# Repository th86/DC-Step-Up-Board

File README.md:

DC-DC Step-Up Board
=========

This is an NE555-based adjustable DC-DC step-up board, which converts 9~12Vdc to up to 400Vdc. 

WARNING: THE HIGH VOLTAGE IS LETHAL, USE IT WITH CAUTION!

## License ##
This project is licensed under the MIT license.

Copyright (c) 2015 Tai-Hsien Ouyang

THE DOCUMENT IS PROVIDED "AS IS", WITHOUT WARRANTY OF ANY KIND, EXPRESS OR IMPLIED, INCLUDING BUT NOT LIMITED TO THE WARRANTIES OF MERCHANTABILITY, FITNESS FOR A PARTICULAR PURPOSE AND NONINFRINGEMENT. IN NO EVENT SHALL THE AUTHORS OR COPYRIGHT HOLDERS BE LIABLE FOR ANY CLAIM, DAMAGES OR OTHER LIABILITY, WHETHER IN AN ACTION OF CONTRACT, TORT OR OTHERWISE, ARISING FROM, OUT OF OR IN CONNECTION WITH THE DOCUMENT OR THE USE OR OTHER DEALINGS IN THE DOCUMENT.

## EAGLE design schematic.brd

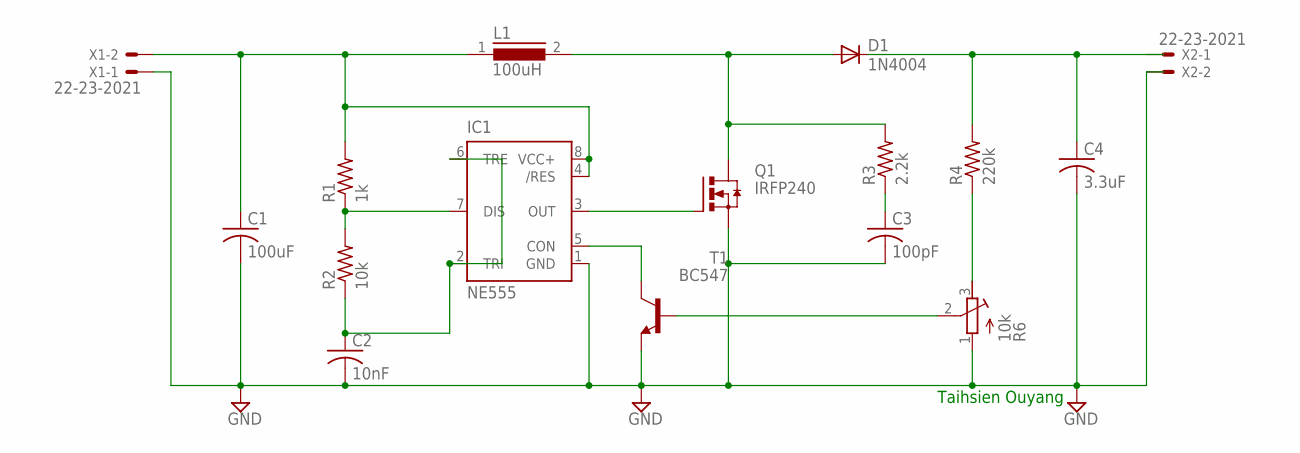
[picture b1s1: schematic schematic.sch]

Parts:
C1: 100uF; C050-025X075
C2: 10nF; C050-025X075
C3: 100pF; C050-025X075
C4: 3.3uF; C050-025X075
D1: 1N4004; DO41-10
IC1: NE555; DIL-08
L1: 100uH; SFT1040
Q1: IRFP240; TO247BV
R1: 1k; 0207/7
R2: 10k; 0207/7
R3: 2.2k; 0207/7
R4: 220k; 0207/7
R6: 10k; RTRIM3339P
T1: BC547; TO92
X1, X2: 22-23-2021

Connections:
GND: C1.2, C2.2, C3.2, C4.2, IC1.1 (GND), Q1.S, R6.1 (A), T1.1 (E), X1.1, X2.2
unnamed: IC1.7 (DIS), R1.1, R2.2
unnamed: C2.1, IC1.2 (TRI), IC1.6 (TRE), R2.1
unnamed: D1.A, L1.2, Q1.D, R3.2
unnamed: IC1.3 (OUT), Q1.G
unnamed: C4.1, D1.C, R4.2, X2.1
unnamed: R4.1, R6.3 (E)
unnamed: R6.2 (S), T1.2 (B)
unnamed: C3.1, R3.1
unnamed: IC1.5 (CON), T1.3 (C)
VCC+: C1.1, IC1.4 (/RES), IC1.8 (VCC+), L1.1, R1.2, X1.2

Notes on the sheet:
Taihsien Ouyang

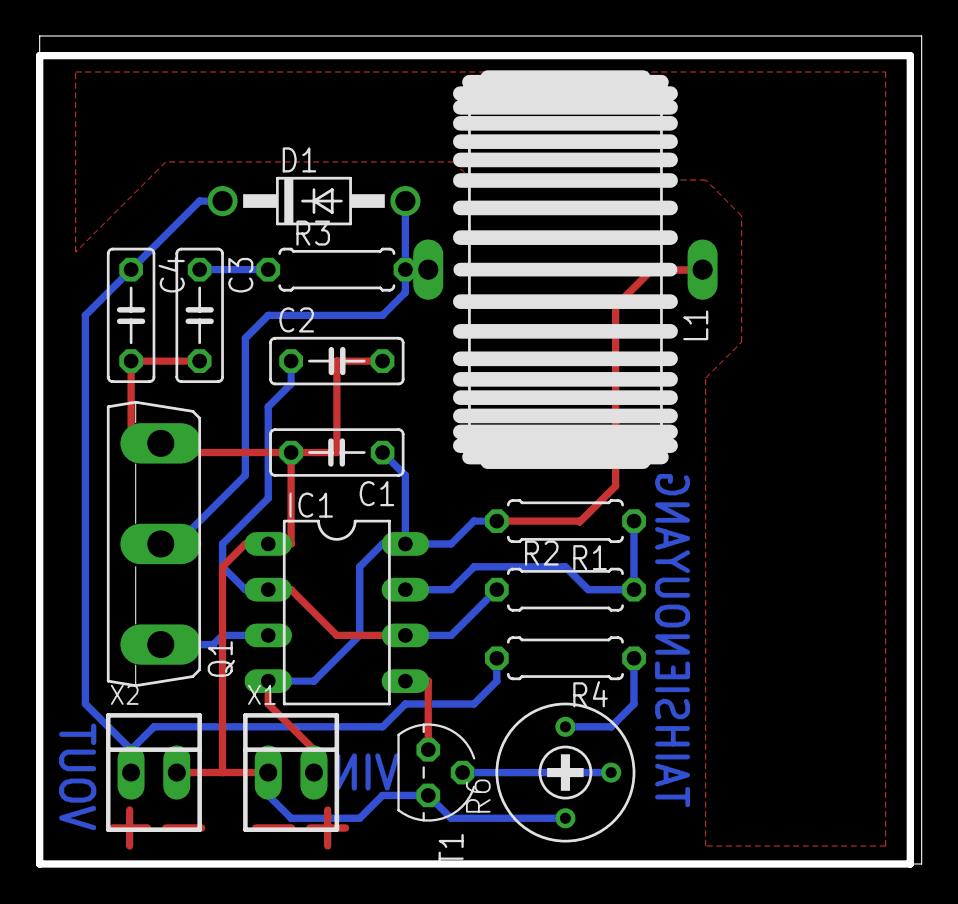
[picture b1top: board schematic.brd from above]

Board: 2 copper layers, 48.8 x 45.8 mm, 16 parts (0 on the bottom side), 11 nets.

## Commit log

2015-11-13 :octocat: Added .gitattributes & .gitignore files
2015-11-13 EAGLE files
    Schematic and PCB
2015-11-13 Readme
